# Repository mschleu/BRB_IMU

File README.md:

# BRB_IMU
nRF52832 based IMU board

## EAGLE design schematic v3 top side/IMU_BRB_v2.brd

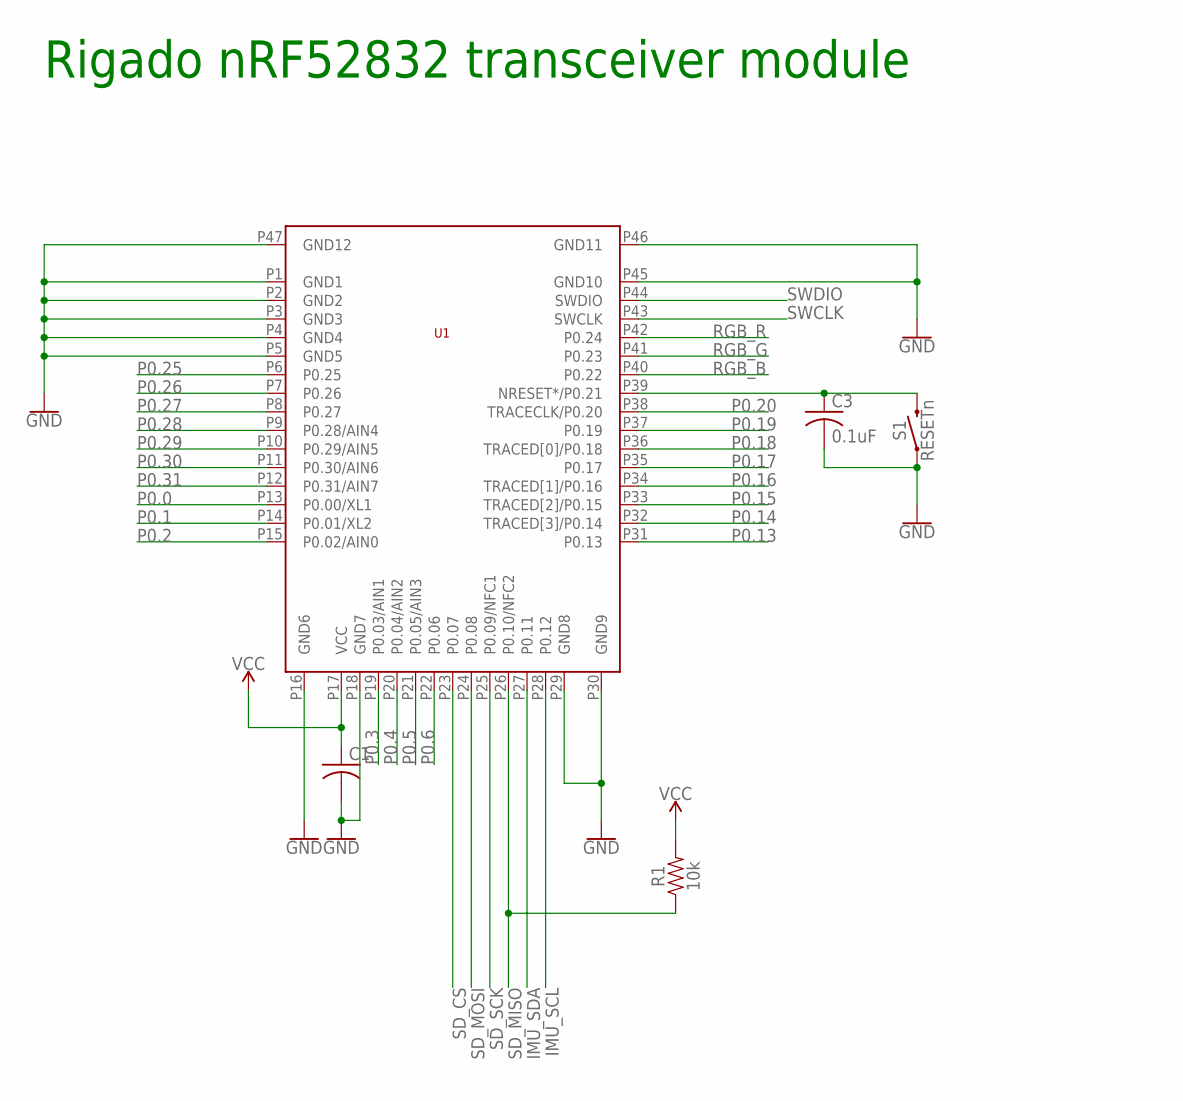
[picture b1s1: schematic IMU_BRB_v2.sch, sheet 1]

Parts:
C1: C-USC0603; C0603
C3: 0.1uF; C0603
R1: 10k; 0603
S1: RESETn; TACTILE_SWITCH_SMD_4.6X2.8MM
U1: BMD-300

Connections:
3V3: C1.1, R1.2, U1.P17 (VCC); also elsewhere on the board
GND: C1.2, C3.2, S1.1, S1.2 (1), U1.P1 (GND1), U1.P2 (GND2), U1.P3 (GND3), U1.P4 (GND4), U1.P5 (GND5), U1.P16 (GND6), U1.P18 (GND7), U1.P29 (GND8), U1.P30 (GND9), U1.P45 (GND10), U1.P46 (GND11), U1.P47 (GND12); also elsewhere on the board
IMU_SCL: U1.P28 (P0.12); also elsewhere on the board
IMU_SDA: U1.P27 (P0.11); also elsewhere on the board
unnamed: C3.1, S1.3 (2), S1.4 (2), U1.P39 (NRESET*/P0.21)
P0.0: U1.P13 (P0.00/XL1)
P0.1: U1.P14 (P0.01/XL2)
P0.2: U1.P15 (P0.02/AIN0)
P0.3: U1.P19 (P0.03/AIN1); also elsewhere on the board
P0.4: U1.P20 (P0.04/AIN2); also elsewhere on the board
P0.5: U1.P21 (P0.05/AIN3); also elsewhere on the board
P0.6: U1.P22 (P0.06); also elsewhere on the board
P0.13: U1.P31 (P0.13)
P0.14: U1.P32 (TRACED[3]/P0.14)
P0.15: U1.P33 (TRACED[2]/P0.15)
P0.16: U1.P34 (TRACED[1]/P0.16)
P0.17: U1.P35 (P0.17)
P0.18: U1.P36 (TRACED[0]/P0.18)
P0.19: U1.P37 (P0.19)
P0.20: U1.P38 (TRACECLK/P0.20)
P0.25: U1.P6 (P0.25)
P0.26: U1.P7 (P0.26)
P0.27: U1.P8 (P0.27)
P0.28: U1.P9 (P0.28/AIN4)
P0.29: U1.P10 (P0.29/AIN5)
P0.30: U1.P11 (P0.30/AIN6)
P0.31: U1.P12 (P0.31/AIN7)
RGB_B: U1.P40 (P0.22); also elsewhere on the board
RGB_G: U1.P41 (P0.23); also elsewhere on the board
RGB_R: U1.P42 (P0.24); also elsewhere on the board
SD_CS: U1.P23 (P0.07); also elsewhere on the board
SD_MISO: R1.1, U1.P26 (P0.10/NFC2); also elsewhere on the board
SD_MOSI: U1.P24 (P0.08); also elsewhere on the board
SD_SCK: U1.P25 (P0.09/NFC1); also elsewhere on the board
SWCLK: U1.P43 (SWCLK); also elsewhere on the board
SWDIO: U1.P44 (SWDIO); also elsewhere on the board

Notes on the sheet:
Rigado nRF52832 transceiver module

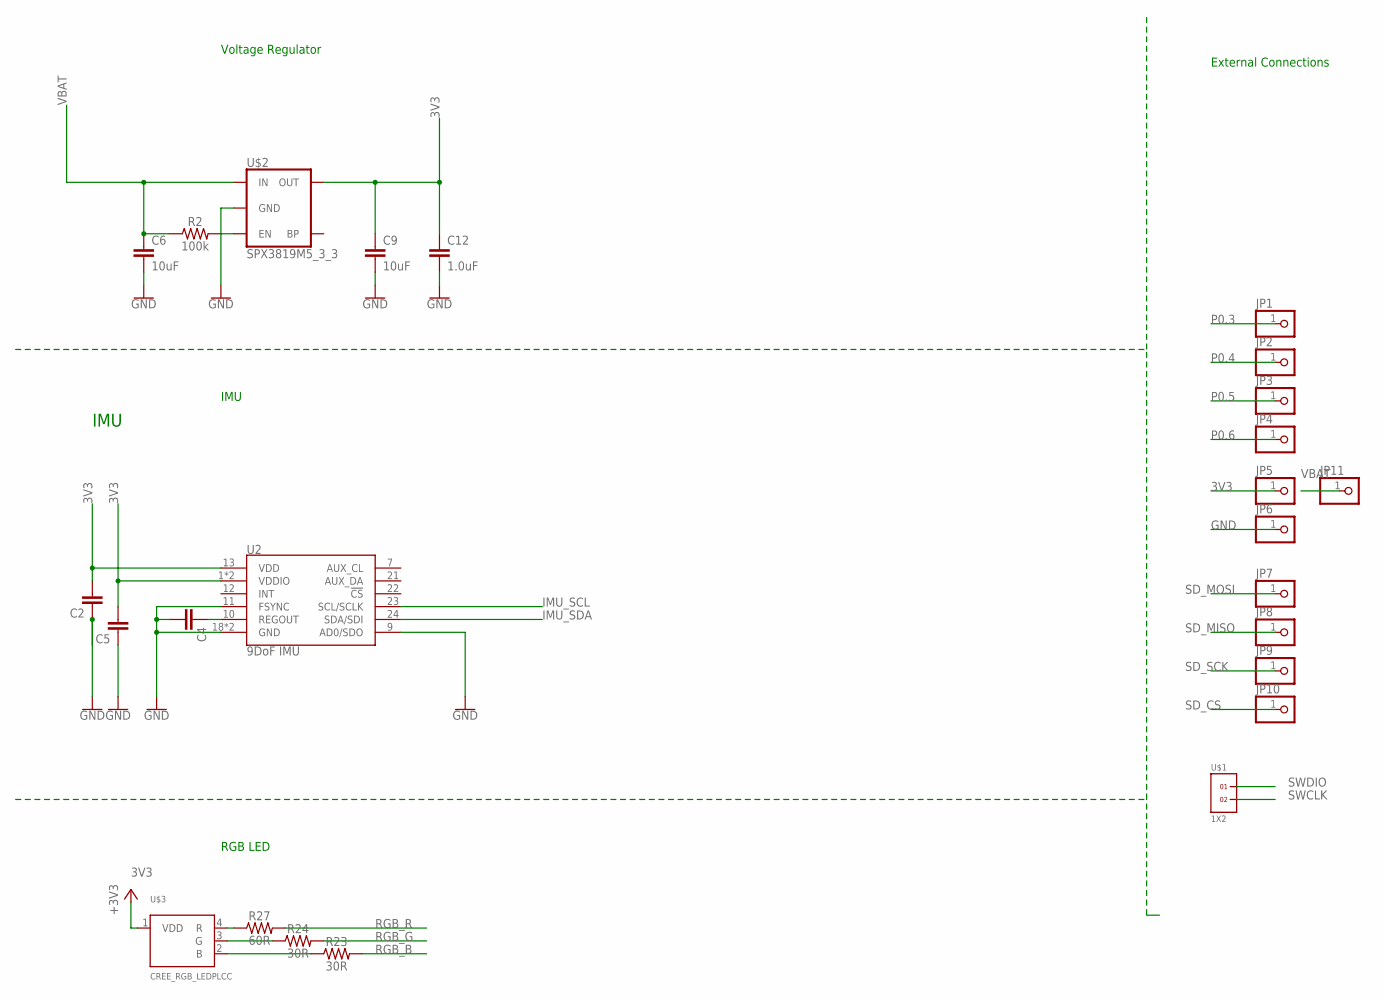
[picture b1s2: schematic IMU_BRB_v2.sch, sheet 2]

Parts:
C2, C4, C5: 0.1UF-0603-25V-(+80/-20%); 0603
C6, C9: 10uF; 0805
C12: 1.0uF; 0603
JP1, JP2, JP3, JP4, JP5, JP6, JP7, JP8, JP9, JP10, JP11: PINHD-1X1; 1X01
R2: 100k; 0603
R23, R24: 30R; 0603
R27: 60R; 0603
U2: 9DoF IMU; QFN24-3X3
U$1: 1X2
U$2: SPX3819M5_3_3; SOT23-5
U$3: CREE_RGB_LEDPLCC; CREE_RGB

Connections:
3V3: C2.2, C5.2, C9.1, C12.1, JP5.1, U2.1 (VDDIO), U2.8 (VDDIO), U2.13 (VDD), U$2.5 (OUT), U$3.1 (VDD); also elsewhere on the board
EN: R2.2, U$2.3 (EN)
GND: C2.1, C4.2, C5.1, C6.2, C9.2, C12.2, JP6.1, U2.11 (FSYNC), U2.18 (GND), U2.20 (GND), U$2.2 (GND); also elsewhere on the board
IMU_SCL: U2.23 (SCL/SCLK); also elsewhere on the board
IMU_SDA: U2.24 (SDA/SDI); also elsewhere on the board
unnamed: C4.1, U2.10 (REGOUT)
unnamed: R27.1, U$3.4 (R)
unnamed: R24.1, U$3.3 (G)
unnamed: R23.1, U$3.2 (B)
P0.3: JP1.1; also elsewhere on the board
P0.4: JP2.1; also elsewhere on the board
P0.5: JP3.1; also elsewhere on the board
P0.6: JP4.1; also elsewhere on the board
RGB_B: R23.2; also elsewhere on the board
RGB_G: R24.2; also elsewhere on the board
RGB_R: R27.2; also elsewhere on the board
SD_CS: JP10.1; also elsewhere on the board
SD_MISO: JP8.1; also elsewhere on the board
SD_MOSI: JP7.1; also elsewhere on the board
SD_SCK: JP9.1; also elsewhere on the board
SWCLK: U$1.2; also elsewhere on the board
SWDIO: U$1.1; also elsewhere on the board
VBAT: C6.1, JP11.1, R2.1, U$2.1 (IN)

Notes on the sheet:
IMU
Voltage Regulator
RGB LED
External Connections

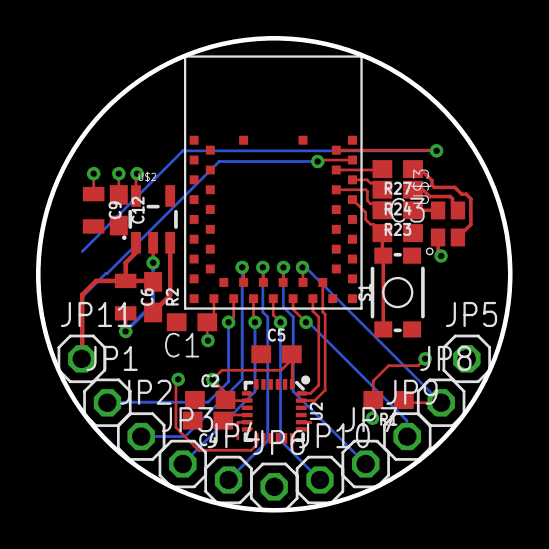
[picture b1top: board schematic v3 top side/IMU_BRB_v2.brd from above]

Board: 2 copper layers, 26.2 x 26.2 mm, 30 parts (1 on the bottom side), 24 nets.

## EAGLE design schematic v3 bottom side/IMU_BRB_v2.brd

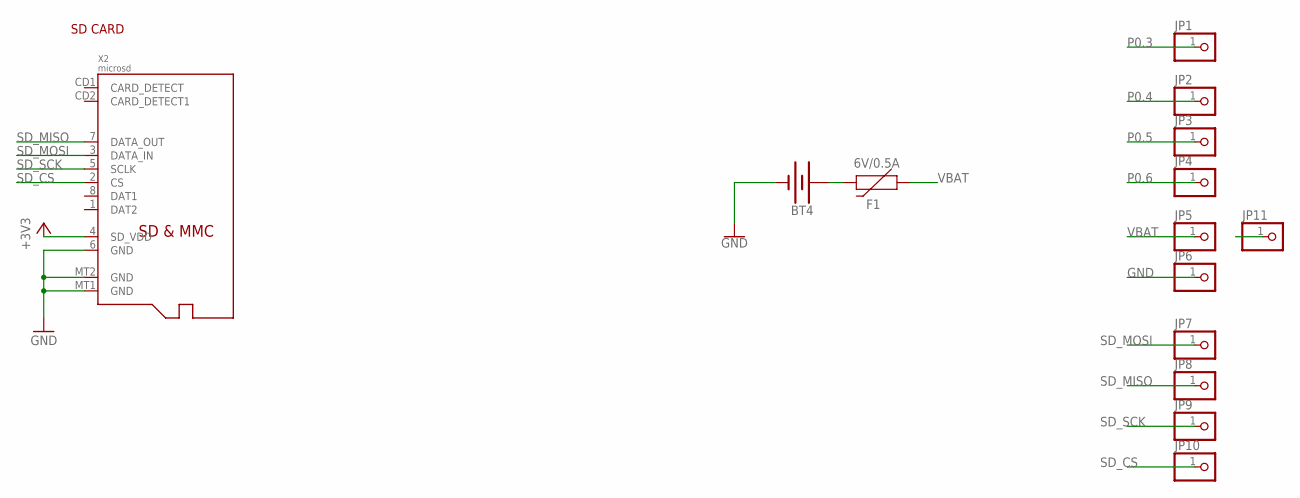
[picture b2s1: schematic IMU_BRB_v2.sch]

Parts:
BT4: BATTERY-20MM_SMD_4LEGS; BATTCON_20MM_4LEGS
F1: 6V/0.5A; 1206
JP1, JP2, JP3, JP4, JP5, JP6, JP7, JP8, JP9, JP10, JP11: PINHD-1X1; 1X01
X2: microsd; MICROSD

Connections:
3V3: JP11.1, X2.4 (SD_VDD)
GND: BT4.NEGATIVE (-), JP6.1, X2.6 (GND), X2.MT1 (GND), X2.MT2 (GND)
unnamed: BT4.POSITIVE@1 (+), BT4.POSITIVE@2 (+), BT4.POSITIVE@3 (+), BT4.POSITIVE@4 (+), F1.2
P0.3: JP1.1
P0.4: JP2.1
P0.5: JP3.1
P0.6: JP4.1
SD_CS: JP10.1, X2.2 (CS)
SD_MISO: JP8.1, X2.7 (DATA_OUT)
SD_MOSI: JP7.1, X2.3 (DATA_IN)
SD_SCK: JP9.1, X2.5 (SCLK)
VBAT: F1.1, JP5.1

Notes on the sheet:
SD CARD

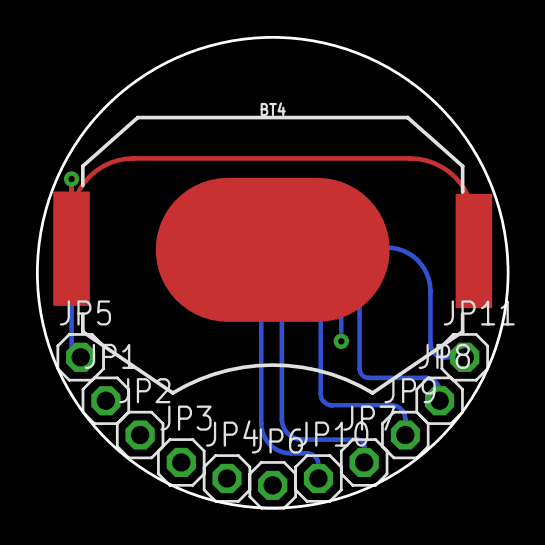
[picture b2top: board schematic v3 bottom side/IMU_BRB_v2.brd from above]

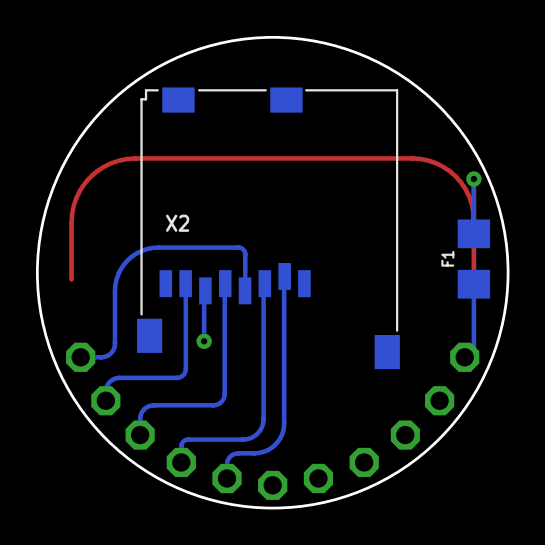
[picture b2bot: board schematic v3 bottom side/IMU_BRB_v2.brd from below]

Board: 2 copper layers, 26.2 x 26.2 mm, 14 parts (2 on the bottom side), 8 nets.

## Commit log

2018-05-09 Source code and hardware

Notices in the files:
parts and their libraries:
microbuilder: This work is placed in the public domain, and may be freely used for commercial and non-commercial work with the following conditions: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
SparkFun-Batteries: Licensing: Creative Commons ShareAlike 4.0 International - https://creativecommons.org/licenses/by-sa/4.0
